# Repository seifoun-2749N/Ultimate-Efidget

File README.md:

# Ultimate-Editget

# Overview :

A custom Efidget made by following the PATHFINDER efidget starter project on Stasis HackClub YSWS event.
Made by love and creativity, includes hard combination to pass it. Requires high IQ level (just kidding)

I chose this project since It's fun to make and be creative so I wanted to give it a shot then testing my friends. Also it feels amazing to see people play with something you made and get stuck sometimes until you help them. Since It's not the first PCB I made so I already know how to make It but by making this DIY game I got more experience dealing with PCB and KiCad pecisely and got better also in making beautiful PCBs.

It comes with 4 LEDs, 4 switches and a buzzer. Your goal is to find out how can you make the 4 leds work at the same time.

### Here is how it works (Don't read this if you don't want to know the solution) :
- Button 1 activates the LED3 if you tapped on the button n times such that n is an even number. If n was an odd number, that means that LED3 and LED4 will be inactivated.
- Button 2 activated LED1 and a timer of 10 seconds (with a buzzer signal) : To activate LED2 you should press button3 3 times before the timer ends or the LEDs will be inactivated
- Button 4 simply turn LED4 on and off by pressing it, nothing special (It's so easy that It could trick the player)

The buzzer will play a quick win song if the players wins

---

# 3D Overview :
## Front View

## Back View

## Schematics

## PCB Design

---

# BOM :
| Id | Designator | Footprint | Qty | Designation | Reference | Total Cost (USD) |
|----|------------|------------|-----|-------------|-----------|------------------|
| 1 | SW2, SW1, SW4, SW3 | SW_Cherry_MX_1.00u_PCB | 4 | SW_Push | [AliExpress](https://ar.aliexpress.com/item/1005006091988869.html?spm=a2g0o.productlist.main.4.2872xBzIxBzIE6&algo_pvid=d44246cc-77cb-43e4-8068-2f2bc8c97c57&aem_p4p_detail=202606091639448252744772420080000779202&algo_exp_id=d44246cc-77cb-43e4-8068-2f2bc8c97c57-3&pdp_ext_f=%7B%22order%22%3A%221335%22%2C%22spu_best_type%22%3A%22price%22%2C%22eval%22%3A%221%22%2C%22fromPage%22%3A%22search%22%7D&pdp_npi=6%40dis%21USD%214.64%213.67%21%21%2131.30%2124.73%21%40213ba8cc17810483843314481ef6ab%2112000035698597715%21sea%21TN%217442585653%21X%211%210%21n_tag%3A-29911%3Bd%3A60442e28%3Bm03_new_user%3A-29895&curPageLogUid=IL7W9u5bs8j8&utparam-url=scene%3Asearch%7Cquery_from%3A%7Cx_object_id%3A1005006091988869%7C_p_origin_prod%3A&search_p4p_id=202606091639448252744772420080000779202_1) | $3.67 |
| 2 | D3, D1, D4, D2 | LEDRD254W57D500H1070 | 4 | L08R5000Q1 | [LitteSon (Local Shop)](https://little-son.tn/accueil/761-123-diode-led-5mm.html#/8-couleur-blanc) | $0.12 |
| 3 | R1, R4, R3, R2 | R_Axial_DIN0204_L3.6mm_D1.6mm_P5.08mm_Horizontal | 4 | R | [LitteSon (Local Shop)](https://little-son.tn/accueil/876-resistance-220ohm-14w.html) | $0.14 |
| 4 | U1 | XIAO-Generic-Hybrid-14P-2.54-21X17.8MM | 1 | MODULE-SEEEDUINO-XIAO | [AliExpress](https://ar.aliexpress.com/item/1005004459618789.html) | $4.85 |
| 5 | BZ1 | Buzzer_12x9.5RM7.6 | 1 | Buzzer | [LittleSon (Local Shop)](https://little-son.tn/accueil/423-buzzer-passif-5v.html) | $0.35 |

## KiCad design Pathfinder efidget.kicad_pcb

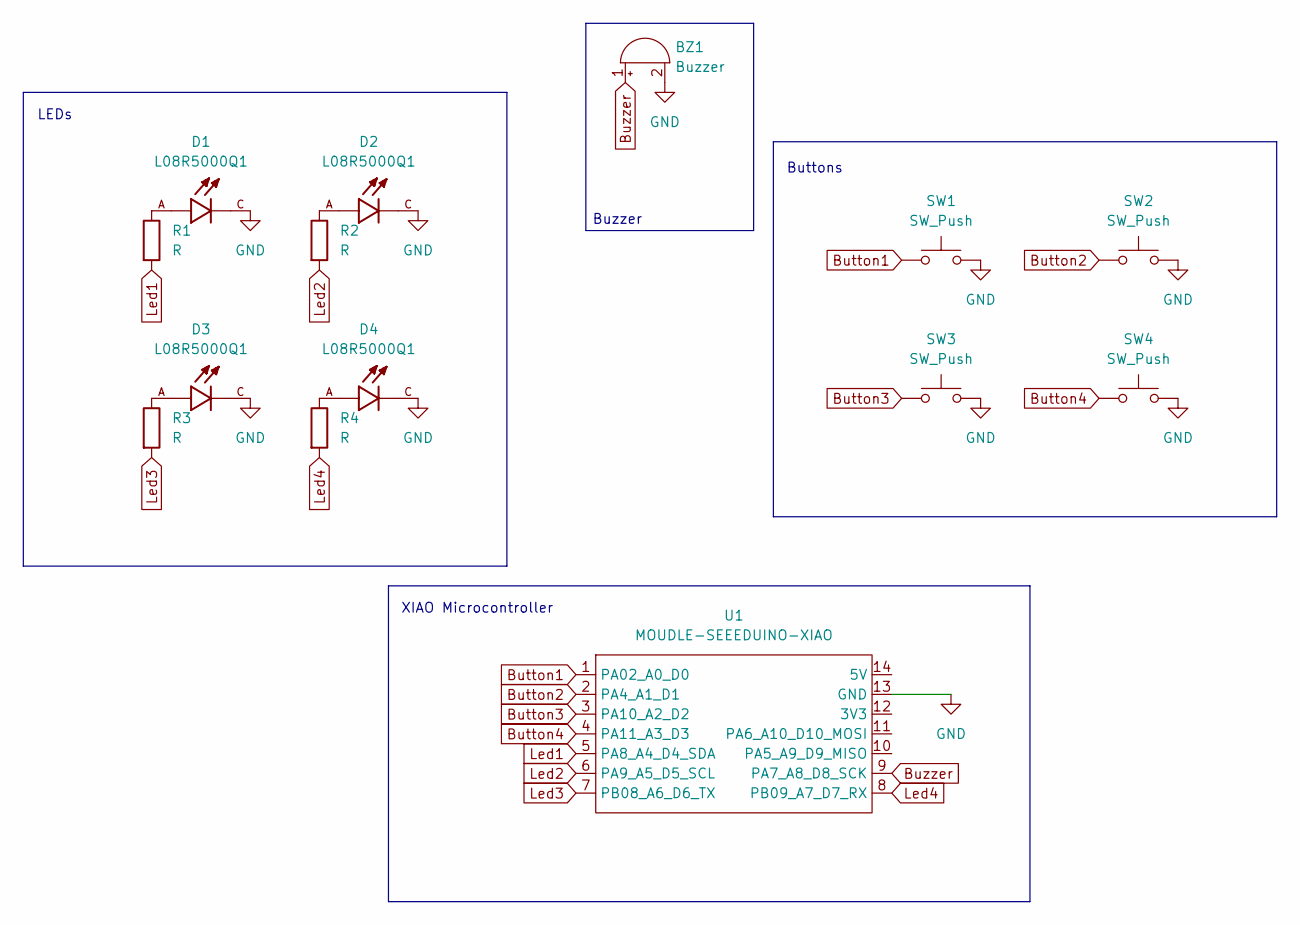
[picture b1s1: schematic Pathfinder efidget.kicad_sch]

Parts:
BZ1: Buzzer
D1, D2, D3, D4: L08R5000Q1; LEDRD254W57D500H1070; PARTREV NA
R1, R2, R3, R4: R
SW1, SW2, SW3, SW4: SW_Push
U1: MOUDLE-SEEEDUINO-XIAO

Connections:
Button1: SW1.1, U1.1 (PA02_A0_D0)
Button2: SW2.1, U1.2 (PA4_A1_D1)
Button3: SW3.1, U1.3 (PA10_A2_D2)
Button4: SW4.1, U1.4 (PA11_A3_D3)
Buzzer: BZ1.1 (+), U1.9 (PA7_A8_D8_SCK)
GND: BZ1.2 (-), D1.C, D2.C, D3.C, D4.C, SW1.2, SW2.2, SW3.2, SW4.2, U1.13 (GND)
Led1: R1.2, U1.5 (PA8_A4_D4_SDA)
Led2: R2.2, U1.6 (PA9_A5_D5_SCL)
Led3: R3.2, U1.7 (PB08_A6_D6_TX)
Led4: R4.2, U1.8 (PB09_A7_D7_RX)
unnamed: D1.A, R1.1
unnamed: D2.A, R2.1
unnamed: D3.A, R3.1
unnamed: D4.A, R4.1

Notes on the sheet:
LEDs
XIAO Microcontroller
Buzzer
Buttons

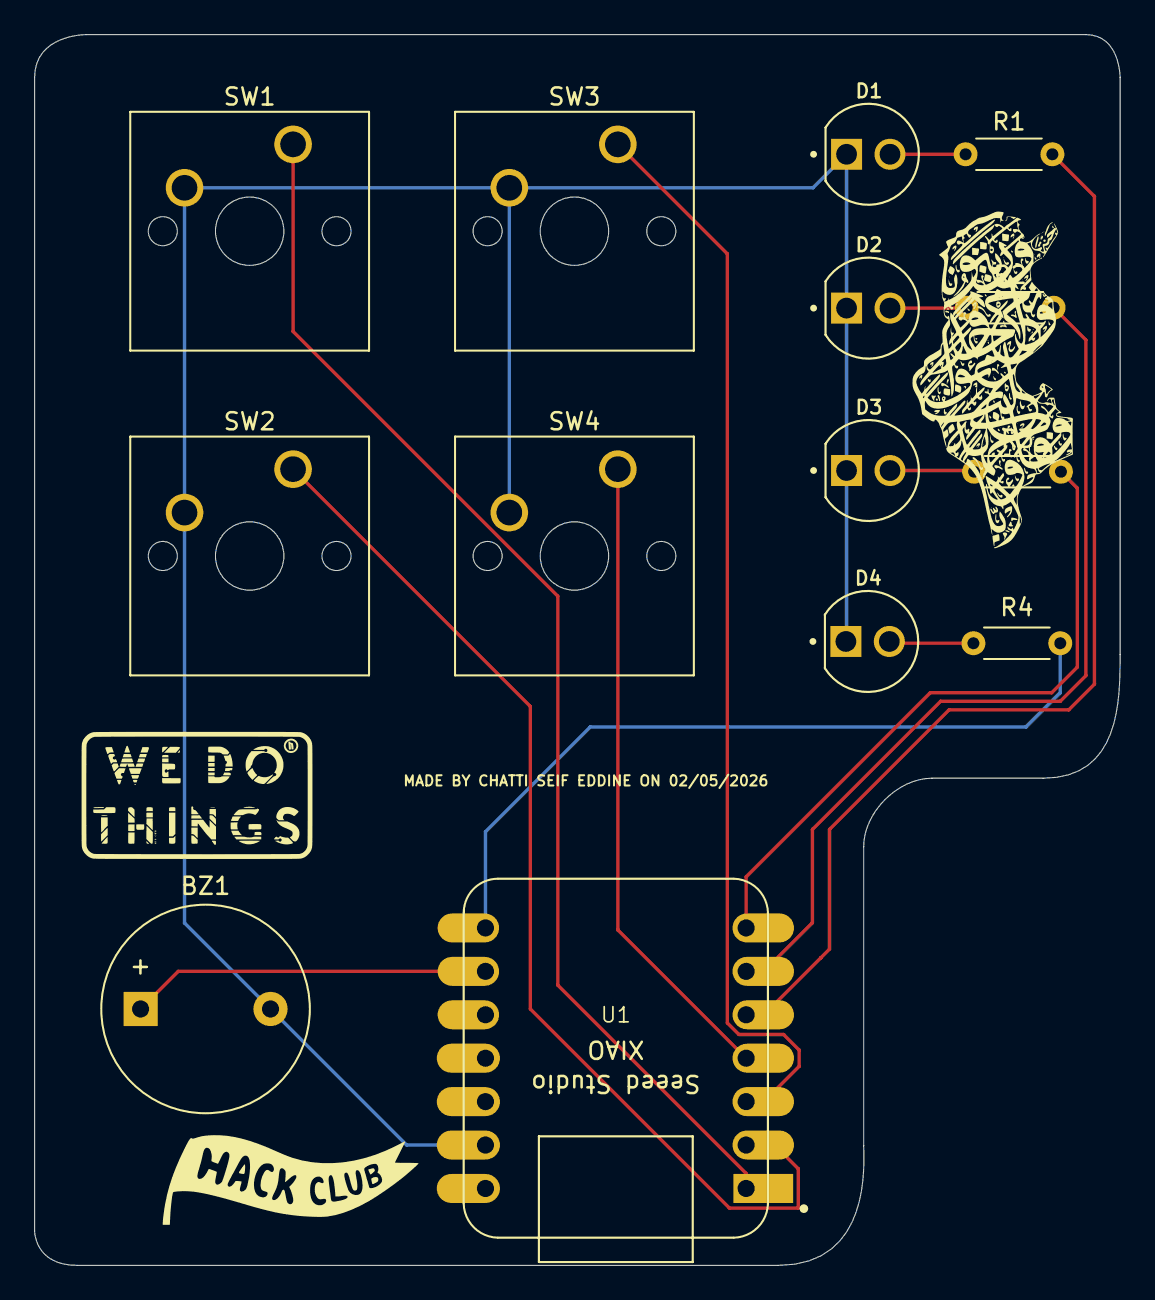
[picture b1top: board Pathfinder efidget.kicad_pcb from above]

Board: 2 copper layers, 63.5 x 72.0 mm, 14 parts (0 on the bottom side), 14 nets.

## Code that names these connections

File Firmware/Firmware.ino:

int BUT1 = D0;
int BUT2 = D1;
int BUT3 = D2;
int BUT4 = D3;

int LED1 = D4;
int LED2 = D5;
int LED3 = D6;
int LED4 = D7;

int BUZZ = D8;

bool timerRunning = false;

void setup() {
  pinMode(BUT1,INPUT_PULLUP);
  pinMode(BUT2,INPUT_PULLUP);
  pinMode(BUT3,INPUT_PULLUP);
  pinMode(BUT4,INPUT_PULLUP);

  pinMode(LED1,OUTPUT);
  pinMode(LED2,OUTPUT);
  pinMode(LED3,OUTPUT);
  pinMode(LED4,OUTPUT);

  pinMode(BUZZ,OUTPUT);
  long startTime = millis();

}

void loop() {
  int but1press = 0;
  long but2time;
  timerRunning  = true;
  if (digitalRead(BUT1) == HIGH) {
    but1press++;
    if (but1press%2 == 0){
      digitalWrite(LED3, HIGH);
    }
    else{
      digitalWrite(LED3, LOW);
      digitalWrite(LED4, LOW);
    }
  }
  else {
    digitalWrite(LED3, LOW);
  }
  if (digitalRead(BUT2) == HIGH) {
    timerRunning = true;
    but2time = millis();
    digitalWrite(LED1, HIGH);
    for(int i=0; i<3; i++){
      digitalWrite(BUZZ, HIGH);
      delay(200);
      digitalWrite(BUZZ, LOW);
      delay(200);
    }
    int but3press = 0;
    if (digitalRead(BUT3) == HIGH){
      but3press++;
    }
    if (timerRunning){
      if (but3press == 3){
        digitalWrite(LED2, HIGH);
        timerRunning = false;
      }
      else if (millis()-but2time >= 10000){
        digitalWrite(LED1, LOW);
        timerRunning = false;
        but3press = 0;
      }
    }
    if (but3press>3){
      digitalWrite(LED1, LOW);
      digitalWrite(LED2, LOW);
      but3press = 0;
    }
  }

  else{
    digitalWrite(LED1, LOW);
  }

  if (digitalRead(BUT4) == HIGH){
    digitalWrite(LED4, HIGH);
  }
  else{
    digitalWrite(LED4, LOW);
  }
  if(digitalRead(LED1) == HIGH && digitalRead(LED2) == HIGH && digitalRead(LED3) == HIGH && digitalRead(LED4) == HIGH) {
    winSong();
  }
}

void winSong() {
  int melody[] = {262, 330, 392, 523, 392, 523, 659, 784};
  int duration[] = {150, 150, 150, 300, 150, 150, 150, 400};

  for (int i = 0; i < 8; i++) {
    tone(BUZZ, melody[i], duration[i]);
    delay(duration[i] + 50);
  }
  noTone(BUZZ);
}
